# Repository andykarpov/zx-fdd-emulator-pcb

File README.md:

PCB and schematic for ZX FDD Emulator by EvgenRU: https://github.com/EvgeniyRU/ZX_FDD_Emulator

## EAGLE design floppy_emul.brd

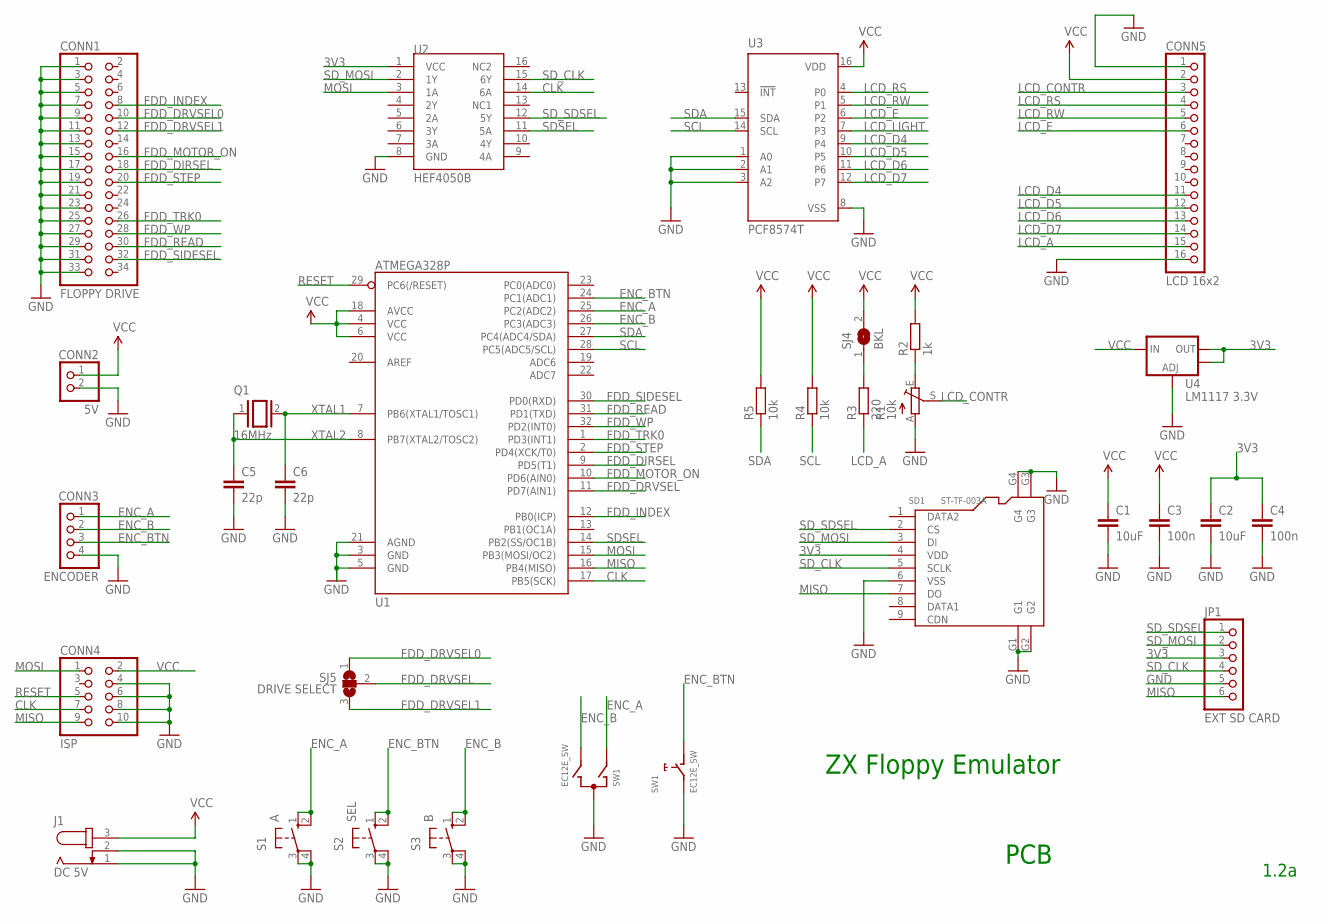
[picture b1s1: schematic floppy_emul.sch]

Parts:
C1, C2: 10uF; C0805
C3, C4: 100n; C0805
C5, C6: 22p; C0805
CONN1: FLOPPY DRIVE; 2X17
CONN2: 5V; 1X02
CONN3: ENCODER; 1X04
CONN4: ISP; 2X05
CONN5: LCD 16x2; 1X16
J1: DC 5V; SPC4077
JP1: EXT SD CARD; 1X06
Q1: 16MHz; QS
R1: 10k; RJ9W
R2: 1k; R0805
R3: 220; R0805
R4, R5: 10k; R0805
S1: A; B3F-10XX
S2: SEL; B3F-10XX
S3: B; B3F-10XX
SD1: ST-TF-003A; MICRO-SD9+4P-SMD-16.1X14.5X1.85MM
SJ4: BKL; SJ
SJ5: DRIVE SELECT; SJ_2
SW1: EC12E_SW; ALPS_EC12E_SW
U1: ATMEGA328P; TQFP32-08
U2: HEF4050B; SO16
U3: PCF8574T; SO16W
U4: LM1117 3.3V; SOT223

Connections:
3V3: C2.1, C4.1, JP1.3, SD1.4 (VDD), U2.1 (VCC), U4.2 (OUT), U4.4 (OUT)
CLK: CONN4.7, U1.17 (PB5(SCK)), U2.14 (6A)
ENC_A: CONN3.1, S1.1 (S), S1.2 (S1), SW1.A, U1.25 (PC2(ADC2))
ENC_B: CONN3.2, S3.1 (S), S3.2 (S1), SW1.B, U1.26 (PC3(ADC3))
ENC_BTN: CONN3.3, S2.1 (S), S2.2 (S1), SW1.D (1), U1.24 (PC1(ADC1))
FDD_DIRSEL: CONN1.18, U1.9 (PD5(T1))
FDD_DRVSEL: SJ5.2, U1.11 (PD7(AIN1))
FDD_DRVSEL0: CONN1.10, SJ5.1
FDD_DRVSEL1: CONN1.12, SJ5.3
FDD_INDEX: CONN1.8, U1.12 (PB0(ICP))
FDD_MOTOR_ON: CONN1.16, U1.10 (PD6(AIN0))
FDD_READ: CONN1.30, U1.31 (PD1(TXD))
FDD_SIDESEL: CONN1.32, U1.30 (PD0(RXD))
FDD_STEP: CONN1.20, U1.2 (PD4(XCK/T0))
FDD_TRK0: CONN1.26, U1.1 (PD3(INT1))
FDD_WP: CONN1.28, U1.32 (PD2(INT0))
GND: C1.2, C2.2, C3.2, C4.2, C5.2, C6.2, CONN1.1, CONN1.3, CONN1.5, CONN1.7, CONN1.9, CONN1.11, CONN1.13, CONN1.15, CONN1.17, CONN1.19, CONN1.21, CONN1.23, CONN1.25, CONN1.27, CONN1.29, CONN1.31, CONN1.33, CONN2.2, CONN3.4, CONN4.4, CONN4.6, CONN4.8, CONN4.10, CONN5.1, CONN5.16, J1.1, J1.2, JP1.5, R1.A, S1.3, S1.4 (P1), S2.3, S2.4 (P1), S3.3, S3.4 (P1), SD1.6 (VSS), SD1.G1, SD1.G2, SD1.G3, SD1.G4, SW1.C, SW1.E (2), U1.3 (GND), U1.5 (GND), U1.21 (AGND), U2.8 (GND), U3.1 (A0), U3.2 (A1), U3.3 (A2), U3.8 (VSS), U4.1 (ADJ)
LCD_A: CONN5.15, R3.1
LCD_CONTR: CONN5.3, R1.S
LCD_D4: CONN5.11, U3.9 (P4)
LCD_D5: CONN5.12, U3.10 (P5)
LCD_D6: CONN5.13, U3.11 (P6)
LCD_D7: CONN5.14, U3.12 (P7)
LCD_E: CONN5.6, U3.6 (P2)
LCD_LIGHT: U3.7 (P3)
LCD_RS: CONN5.4, U3.4 (P0)
LCD_RW: CONN5.5, U3.5 (P1)
MISO: CONN4.9, JP1.6, SD1.7 (DO), U1.16 (PB4(MISO))
MOSI: CONN4.1, U1.15 (PB3(MOSI/OC2)), U2.3 (1A)
unnamed: R1.E, R2.1
unnamed: R3.2, SJ4.1
RESET: CONN4.5, U1.29 (PC6(/RESET))
SCL: R4.1, U1.28 (PC5(ADC5/SCL)), U3.14 (SCL)
SDA: R5.1, U1.27 (PC4(ADC4/SDA)), U3.15 (SDA)
SDSEL: U1.14 (PB2(SS/OC1B)), U2.11 (5A)
SD_CLK: JP1.4, SD1.5 (SCLK), U2.15 (6Y)
SD_MOSI: JP1.2, SD1.3 (DI), U2.2 (1Y)
SD_SDSEL: JP1.1, SD1.2 (CS), U2.12 (5Y)
VCC: C1.1, C3.1, CONN2.1, CONN4.2, CONN5.2, J1.3, R2.2, R4.2, R5.2, SJ4.2, U1.4 (VCC), U1.6 (VCC), U1.18 (AVCC), U3.16 (VDD), U4.3 (IN)
XTAL1: C6.1, Q1.2, U1.7 (PB6(XTAL1/TOSC1))
XTAL2: C5.1, Q1.1, U1.8 (PB7(XTAL2/TOSC2))

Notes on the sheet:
ZX Floppy Emulator
PCB
1.2a

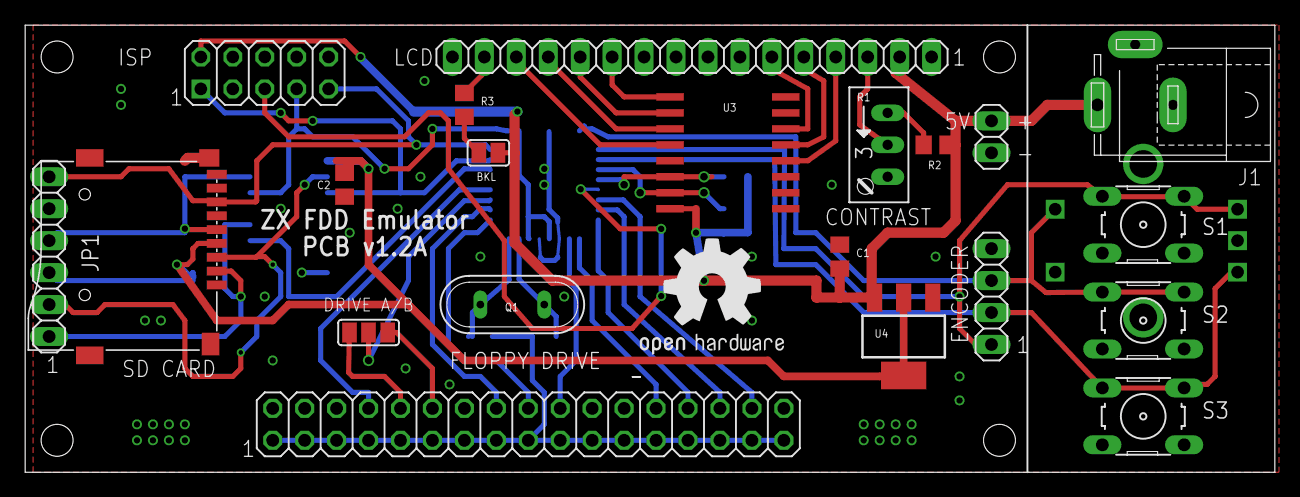
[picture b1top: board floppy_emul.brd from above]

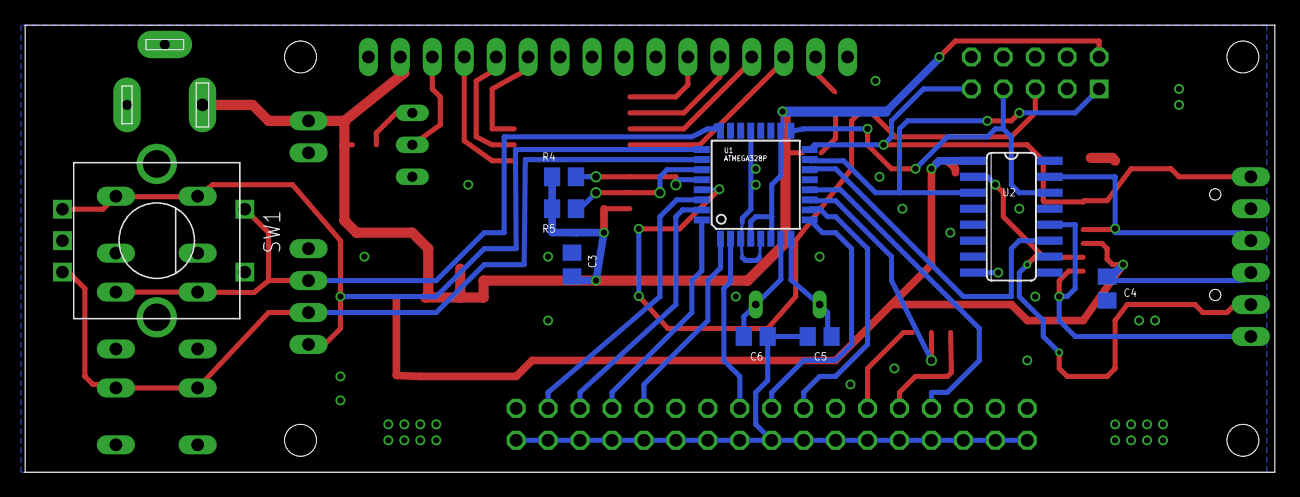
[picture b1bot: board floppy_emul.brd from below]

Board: 2 copper layers, 99.4 x 35.5 mm, 35 parts (9 on the bottom side), 40 nets.

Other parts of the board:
U$1, U$2, U$3, U$4: DRILL_0.1000
U$5: OSHW1

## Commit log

2017-03-10 initial revision
2017-03-10 added gerbers, pdfs
2017-03-10 readme
2017-03-12 Changed SD card connector, added SPI connector for external SD module
2017-03-12 new 3D pcb render
2017-04-14 added photos
2017-04-14 added photos to readme
2017-04-20 Добавлена распиновка разъемов
2017-06-23 board v1.2
2017-06-23 updated gerbers, docs for rev.1.2
2018-01-15 new pcb revision: fixed encoder connections, small improvements
2018-01-15 updated schematics to rev 1.2a
2018-01-15 Updated docs

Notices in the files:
parts and their libraries:
SparkFun-DigitalIC: Licensing: CC v3.0 Share-Alike You are welcome to use this library for commercial purposes.
